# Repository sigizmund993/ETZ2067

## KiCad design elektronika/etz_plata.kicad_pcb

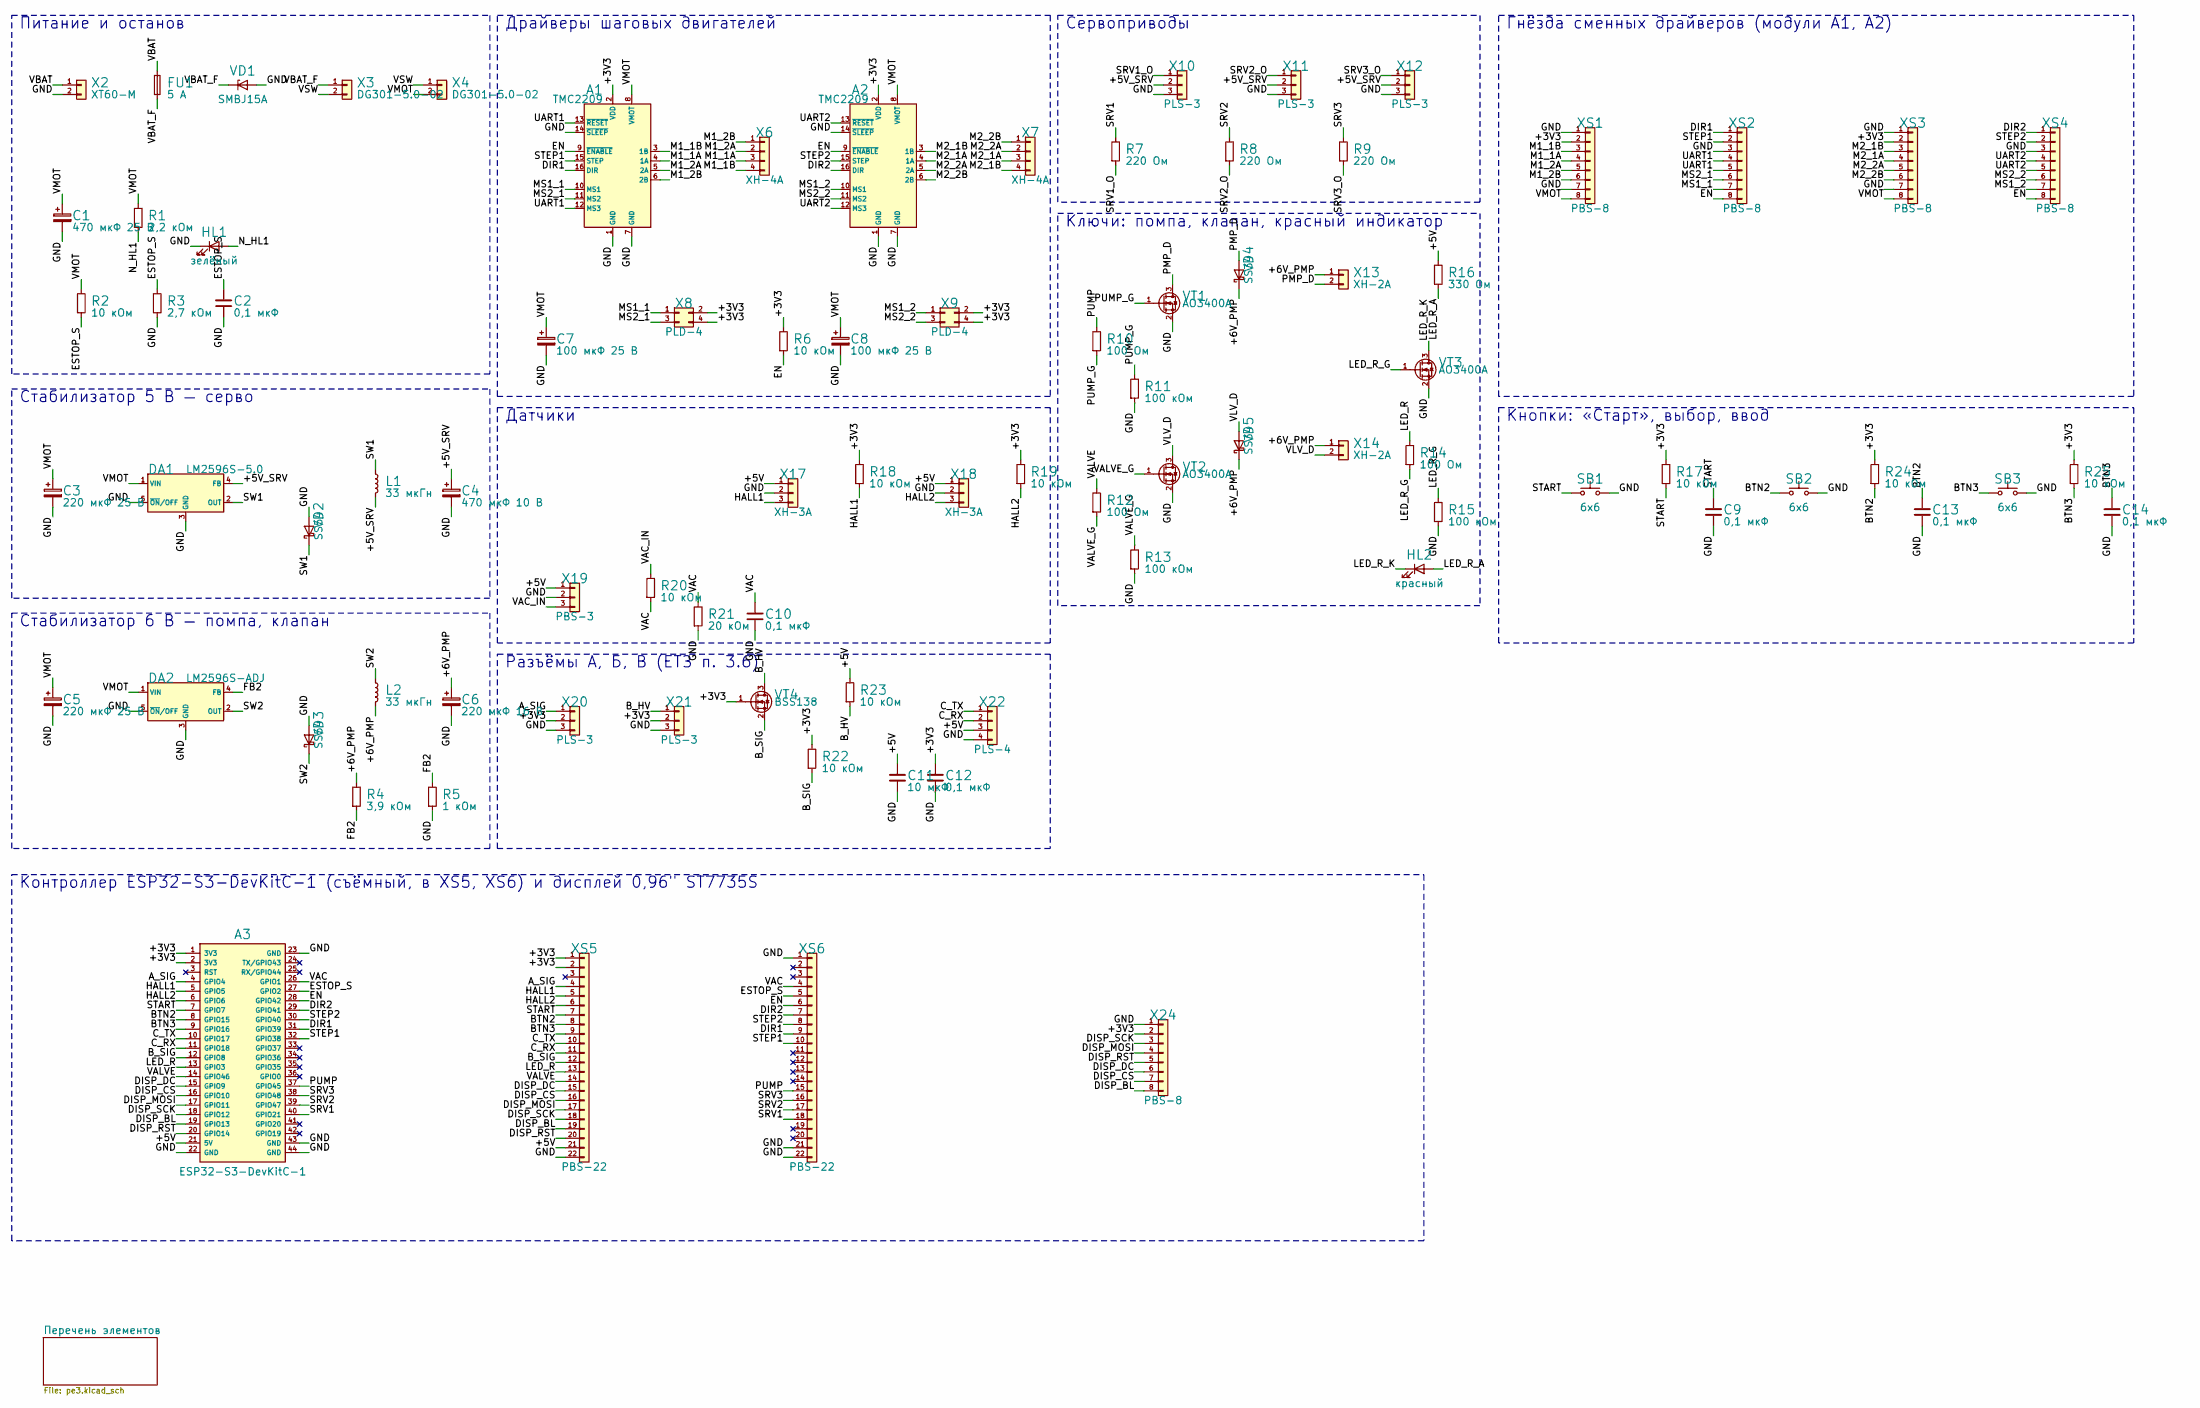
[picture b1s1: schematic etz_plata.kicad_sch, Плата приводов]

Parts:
A1, A2: TMC2209
A3: ESP32-S3-DevKitC-1
C1: 470 мкФ 25 В; CP_Radial_D10.0mm_P5.00mm
C2, C9, C10, C12, C13, C14: 0,1 мкФ; C_0805_2012Metric
C3, C5: 220 мкФ 25 В; CP_Radial_D8.0mm_P3.50mm
C4: 470 мкФ 10 В; CP_Radial_D8.0mm_P3.50mm
C6: 220 мкФ 16 В; CP_Radial_D8.0mm_P3.50mm
C7, C8: 100 мкФ 25 В; CP_Radial_D6.3mm_P2.50mm
C11: 10 мкФ; C_1206_3216Metric
DA1: LM2596S-5.0; TO-263-5_TabPin3
DA2: LM2596S-ADJ; TO-263-5_TabPin3
FU1: 5 А; Fuseholder_Blade_Mini_Keystone_3568
HL1: зелёный; LED_D5.0mm
HL2: красный; LED_D5.0mm
L1, L2: 33 мкГн; L_Bourns_SRR1260
R1: 2,2 кОм; R_0805_2012Metric
R2, R6, R17, R18, R19, R20, R22, R23, R24, R25: 10 кОм; R_0805_2012Metric
R3: 2,7 кОм; R_0805_2012Metric
R4: 3,9 кОм; R_0805_2012Metric
R5: 1 кОм; R_0805_2012Metric
R7, R8, R9: 220 Ом; R_0805_2012Metric
R10, R12, R14: 100 Ом; R_0805_2012Metric
R11, R13, R15: 100 кОм; R_0805_2012Metric
R16: 330 Ом; R_0805_2012Metric
R21: 20 кОм; R_0805_2012Metric
SB1, SB2, SB3: 6x6; SW_PUSH_6mm_H8.5mm
VD1: SMBJ15A; D_SMB
VD2, VD3: SS54; D_SMC
VD4, VD5: SS34; D_SMA
VT1, VT2, VT3: AO3400A; SOT-23
VT4: BSS138; SOT-23
X2: XT60-M; AMASS_XT60-M_1x02_P7.20mm_Vertical
X3, X4: DG301-5.0-02; TerminalBlock_Phoenix_MKDS-1,5-2-5.08_1x02_P5.08mm_Horizont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
X6, X7: XH-4A; JST_XH_B4B-XH-A_1x04_P2.50mm_Vertical
X8, X9: PLD-4; PinHeader_2x02_P2.54mm_Vertical
X10, X11, X12, X20, X21: PLS-3; PinHeader_1x03_P2.54mm_Vertical
X13, X14: XH-2A; JST_XH_B2B-XH-A_1x02_P2.50mm_Vertical
X17, X18: XH-3A; JST_XH_B3B-XH-A_1x03_P2.50mm_Vertical
X19: PBS-3; PinSocket_1x03_P2.54mm_Vertical
X22: PLS-4; PinHeader_1x04_P2.54mm_Vertical
X24: PBS-8; PinSocket_1x08_P2.54mm_Vertical
XS1, XS2, XS3, XS4: PBS-8; PinSocket_1x08_P2.54mm_Vertical
XS5, XS6: PBS-22; PinSocket_1x22_P2.54mm_Vertical

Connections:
/+3V3: A1.2 (VDD), A2.2 (VDD), A3.1 (3V3), A3.2 (3V3), C12.1, R6.1, R17.1, R18.1, R19.1, R22.1, R24.1, R25.1, VT4.1 (G), X8.2, X8.4, X9.2, X9.4, X20.2, X21.2, X24.2, XS1.2, XS3.2, XS5.1, XS5.2
/+5V: A3.21 (5V), C11.1, R16.1, R23.1, X17.1, X18.1, X19.1, X22.3, XS5.21
/+5V_SRV: C4.1, DA1.4 (FB), L1.2, X10.2, X11.2, X12.2
/+6V_PMP: C6.1, L2.2, R4.1, VD4.1 (K), VD5.1 (K), X13.1, X14.1
/A_SIG: A3.4 (GPIO4), X20.1, XS5.4
/BTN2: A3.8 (GPIO15), C13.1, R24.2, SB2.1, XS5.8
/BTN3: A3.9 (GPIO16), C14.1, R25.2, SB3.1, XS5.9
/B_HV: R23.2, VT4.3 (D), X21.1
/B_SIG: A3.12 (GPIO8), R22.2, VT4.2 (S), XS5.12
/C_RX: A3.11 (GPIO18), X22.2, XS5.11
/C_TX: A3.10 (GPIO17), X22.1, XS5.10
/DIR1: A1.16 (DIR), A3.31 (GPIO39), XS2.1, XS6.9
/DIR2: A2.16 (DIR), A3.29 (GPIO41), XS4.1, XS6.7
/DISP_BL: A3.19 (GPIO13), X24.8, XS5.19
/DISP_CS: A3.16 (GPIO10), X24.7, XS5.16
/DISP_DC: A3.15 (GPIO9), X24.6, XS5.15
/DISP_MOSI: A3.17 (GPIO11), X24.4, XS5.17
/DISP_RST: A3.20 (GPIO14), X24.5, XS5.20
/DISP_SCK: A3.18 (GPIO12), X24.3, XS5.18
/EN: A1.9 (~ENABLE), A2.9 (~ENABLE), A3.28 (GPIO42), R6.2, XS2.8, XS4.8, XS6.6
/ESTOP_S: A3.27 (GPIO2), C2.1, R2.2, R3.1, XS6.5
/FB2: DA2.4 (FB), R4.2, R5.1
/GND: A1.1 (GND), A1.7 (GND), A1.14 (~SLEEP), A2.1 (GND), A2.7 (GND), A2.14 (~SLEEP), A3.22 (GND), A3.23 (GND), A3.43 (GND), A3.44 (GND), C1.2, C2.2, C3.2, C4.2, C5.2, C6.2, C7.2, C8.2, C9.2, C10.2, C11.2, C12.2, C13.2, C14.2, DA1.3 (GND), DA1.5 (~ON/OFF), DA2.3 (GND), DA2.5 (~ON/OFF), HL1.1 (K), R3.2, R5.2, R11.2, R13.2, R15.2, R21.2, SB1.2, SB2.2, SB3.2, VD1.2 (A), VD2.2 (A), VD3.2 (A), VT1.2 (S), VT2.2 (S), VT3.2 (S), X2.2, X10.3, X11.3, X12.3, X17.2, X18.2, X19.2, X20.3, X21.3, X22.4, X24.1, XS1.1, XS1.7, XS2.3, XS3.1, XS3.7, XS4.3, XS5.22, XS6.1, XS6.21, XS6.22
/HALL1: A3.5 (GPIO5), R18.2, X17.3, XS5.5
/HALL2: A3.6 (GPIO6), R19.2, X18.3, XS5.6
/LED_R: A3.13 (GPIO3), R14.1, XS5.13
/LED_R_A: HL2.2 (A), R16.2
/LED_R_G: R14.2, R15.1, VT3.1 (G)
/LED_R_K: HL2.1 (K), VT3.3 (D)
/M1_1A: A1.4 (1A), X6.3, XS1.4
/M1_1B: A1.3 (1B), X6.4, XS1.3
/M1_2A: A1.5 (2A), X6.2, XS1.5
/M1_2B: A1.6 (2B), X6.1, XS1.6
/M2_1A: A2.4 (1A), X7.3, XS3.4
/M2_1B: A2.3 (1B), X7.4, XS3.3
/M2_2A: A2.5 (2A), X7.2, XS3.5
/M2_2B: A2.6 (2B), X7.1, XS3.6
/MS1_1: A1.10 (MS1), X8.1, XS2.7
/MS1_2: A2.10 (MS1), X9.1, XS4.7
/MS2_1: A1.11 (MS2), X8.3, XS2.6
/MS2_2: A2.11 (MS2), X9.3, XS4.6
/N_HL1: HL1.2 (A), R1.2
/PMP_D: VD4.2 (A), VT1.3 (D), X13.2
/PUMP: A3.37 (GPIO45), R10.1, XS6.15
/PUMP_G: R10.2, R11.1, VT1.1 (G)
/SRV1: A3.40 (GPIO21), R7.1, XS6.18
/SRV1_O: R7.2, X10.1
/SRV2: A3.39 (GPIO47), R8.1, XS6.17
/SRV2_O: R8.2, X11.1
/SRV3: A3.38 (GPIO48), R9.1, XS6.16
/SRV3_O: R9.2, X12.1
/START: A3.7 (GPIO7), C9.1, R17.2, SB1.1, XS5.7
/STEP1: A1.15 (STEP), A3.32 (GPIO38), XS2.2, XS6.10
/STEP2: A2.15 (STEP), A3.30 (GPIO40), XS4.2, XS6.8
/SW1: DA1.2 (OUT), L1.1, VD2.1 (K)
/SW2: DA2.2 (OUT), L2.1, VD3.1 (K)
/UART1: A1.12 (MS3), A1.13 (~RESET), XS2.4, XS2.5
/UART2: A2.12 (MS3), A2.13 (~RESET), XS4.4, XS4.5
/VAC: A3.26 (GPIO1), C10.1, R20.2, R21.1, XS6.4
/VAC_IN: R20.1, X19.3
/VALVE: A3.14 (GPIO46), R12.1, XS5.14
/VALVE_G: R12.2, R13.1, VT2.1 (G)
/VBAT: FU1.1, X2.1
/VBAT_F: FU1.2, VD1.1 (K), X3.1
/VLV_D: VD5.2 (A), VT2.3 (D), X14.2
/VMOT: A1.8 (VMOT), A2.8 (VMOT), C1.1, C3.1, C5.1, C7.1, C8.1, DA1.1 (VIN), DA2.1 (VIN), R1.1, R2.1, X4.2, XS1.8, XS3.8
/VSW: X3.2, X4.1

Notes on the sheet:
Питание и останов
Стабилизатор 5 В — серво
Стабилизатор 6 В — помпа, клапан
Драйверы шаговых двигателей
Сервоприводы
Датчики
Разъёмы А, Б, В (ЕТЗ п. 3.6)
Ключи: помпа, клапан, красный индикатор
Гнёзда сменных драйверов (модули A1, A2)
Кнопки: «Старт», выбор, ввод
Контроллер ESP32-S3-DevKitC-1 (съёмный, в XS5, XS6) и дисплей 0,96" ST7735S

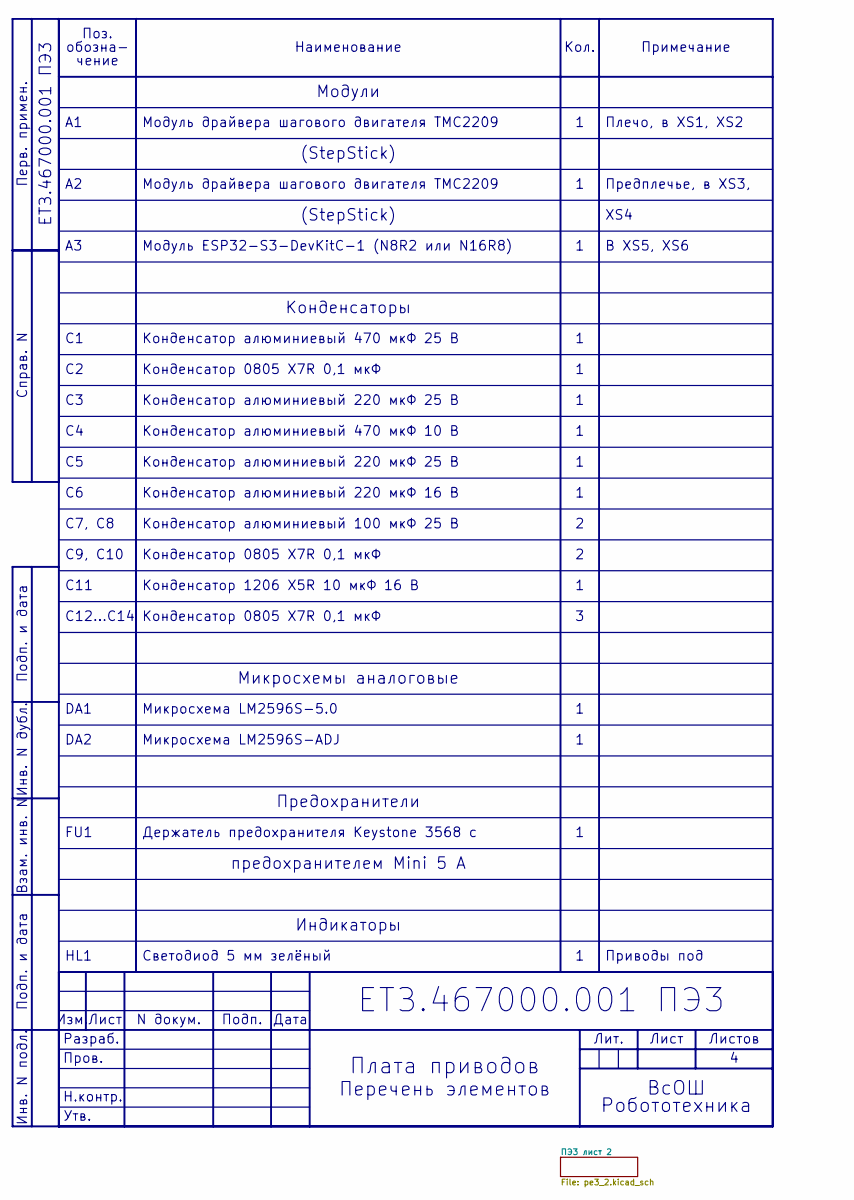
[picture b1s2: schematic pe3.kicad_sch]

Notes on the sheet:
Изм.
Лист
N докум.
Подп.
Дата
Разраб.
Пров.
Н.контр.
Утв.
Лит.
Листов
ЕТЗ.467000.001 ПЭ3
Плата приводов
Перечень элементов
ВсОШ
Робототехника
Инв. N подл.
Подп. и дата
Взам. инв. N
Инв. N дубл.
Перв. примен.
Справ. N
Поз.
обозна-
чение
Наименование
Кол.
Примечание
Модули
Модуль драйвера шагового двигателя TMC2209
Плечо, в XS1, XS2
(StepStick)
Предплечье, в XS3,
XS4
Модуль ESP32-S3-DevKitC-1 (N8R2 или N16R8)
В XS5, XS6
Конденсаторы
Конденсатор алюминиевый 470 мкФ 25 В
Конденсатор 0805 X7R 0,1 мкФ
Конденсатор алюминиевый 220 мкФ 25 В

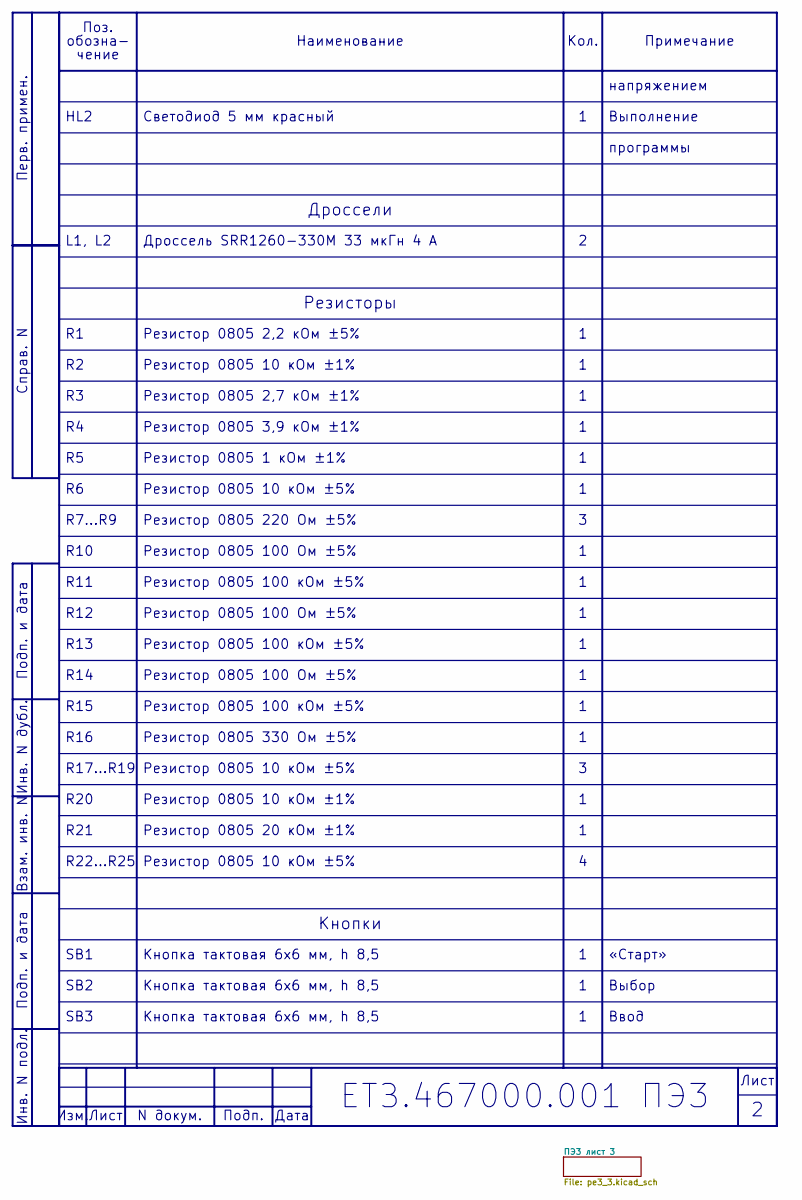
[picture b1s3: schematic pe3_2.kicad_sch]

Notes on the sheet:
Изм.
Лист
N докум.
Подп.
Дата
ЕТЗ.467000.001 ПЭ3
Инв. N подл.
Подп. и дата
Взам. инв. N
Инв. N дубл.
Перв. примен.
Справ. N
Поз.
обозна-
чение
Наименование
Кол.
Примечание
напряжением
HL2
Светодиод 5 мм красный
Выполнение
программы
Дроссели
L1, L2
Дроссель SRR1260-330M 33 мкГн 4 А
Резисторы
Резистор 0805 2,2 кОм ±5%
Резистор 0805 10 кОм ±1%
Резистор 0805 2,7 кОм ±1%
Резистор 0805 3,9 кОм ±1%
Резистор 0805 1 кОм ±1%
Резистор 0805 10 кОм ±5%
R7…R9
Резистор 0805 220 Ом ±5%
R10
Резистор 0805 100 Ом ±5%
R11
Резистор 0805 100 кОм ±5%
R12

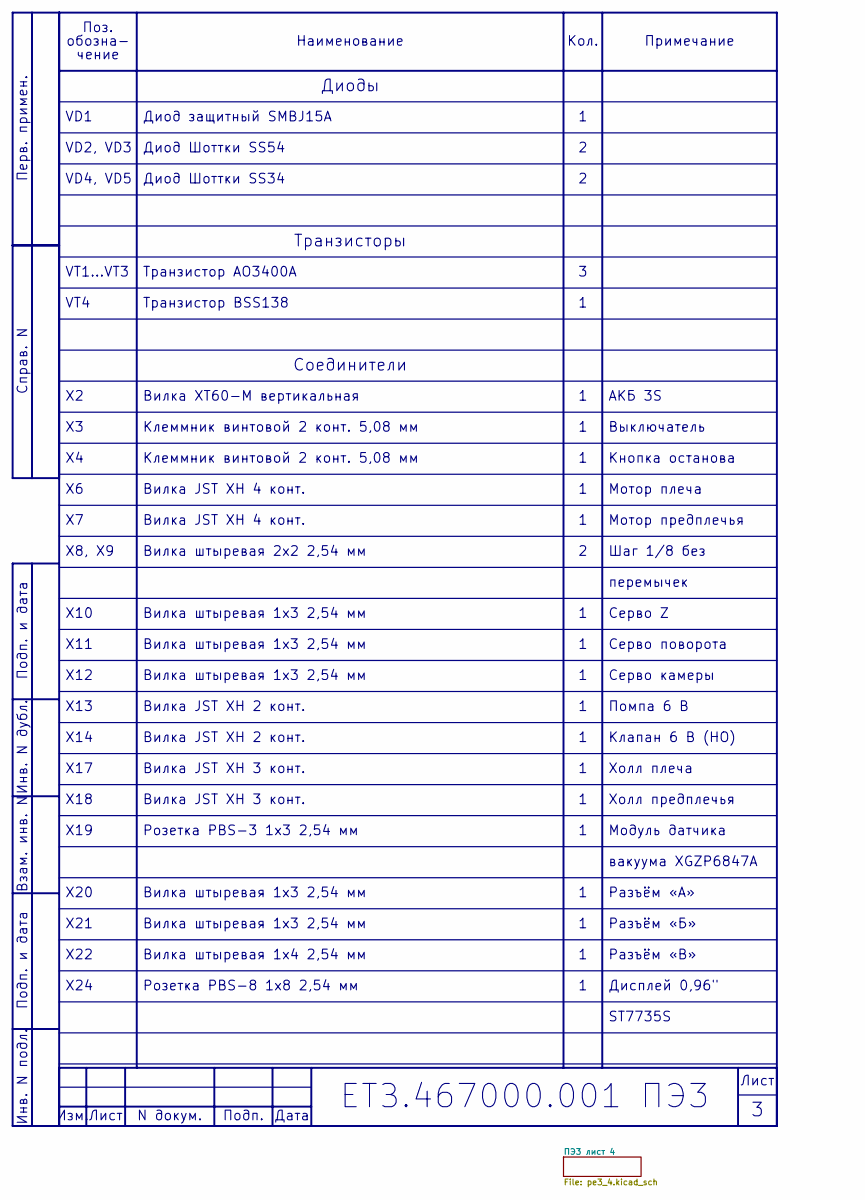
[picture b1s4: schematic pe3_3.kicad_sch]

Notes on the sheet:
Изм.
Лист
N докум.
Подп.
Дата
ЕТЗ.467000.001 ПЭ3
Инв. N подл.
Подп. и дата
Взам. инв. N
Инв. N дубл.
Перв. примен.
Справ. N
Поз.
обозна-
чение
Наименование
Кол.
Примечание
Диоды
VD1
Диод защитный SMBJ15A
VD2, VD3
Диод Шоттки SS54
VD4, VD5
Диод Шоттки SS34
Транзисторы
VT1…VT3
Транзистор AO3400A
VT4
Транзистор BSS138
Соединители
Вилка XT60-M вертикальная
АКБ 3S
Клеммник винтовой 2 конт. 5,08 мм
Выключатель
Кнопка останова
Вилка JST XH 4 конт.
Мотор плеча
Мотор предплечья
X8, X9

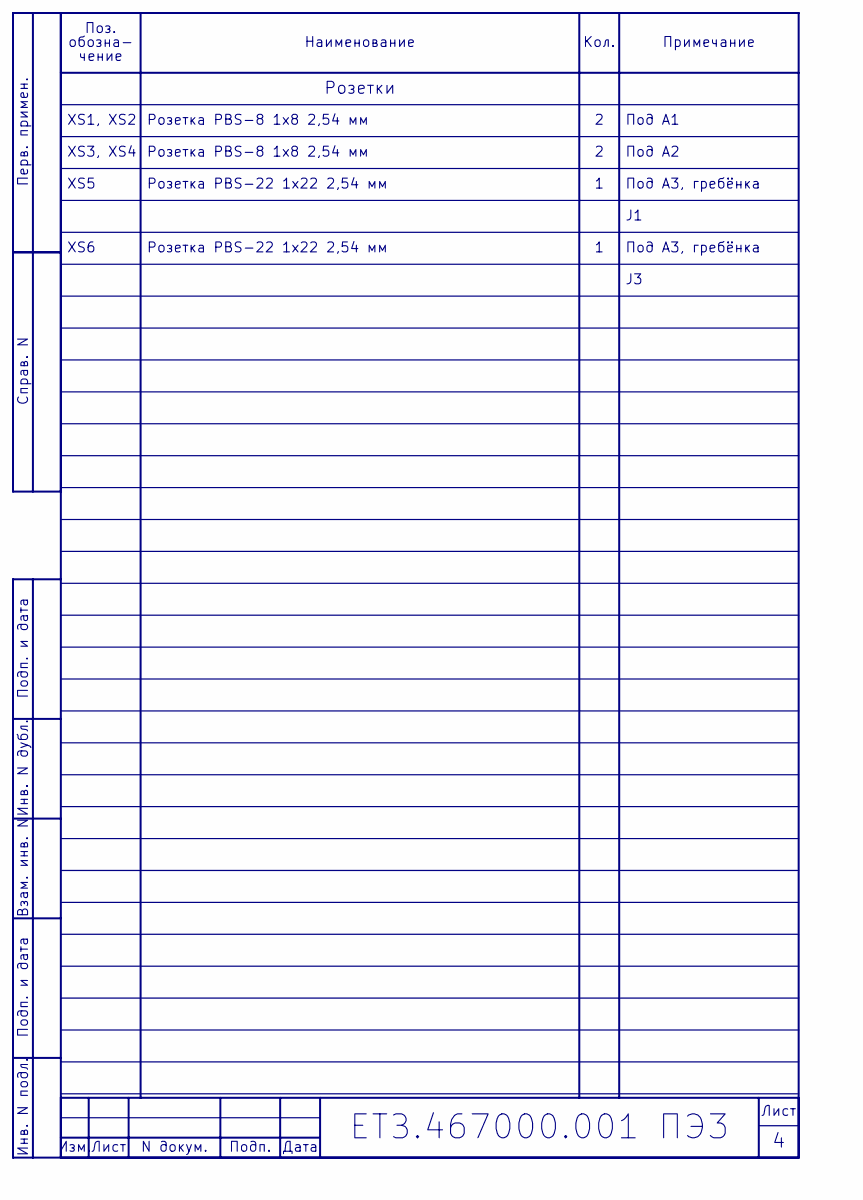
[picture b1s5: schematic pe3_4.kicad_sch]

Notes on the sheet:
Изм.
Лист
N докум.
Подп.
Дата
ЕТЗ.467000.001 ПЭ3
Инв. N подл.
Подп. и дата
Взам. инв. N
Инв. N дубл.
Перв. примен.
Справ. N
Поз.
обозна-
чение
Наименование
Кол.
Примечание
Розетки
XS1, XS2
Розетка PBS-8 1x8 2,54 мм
Под A1
XS3, XS4
Под A2
XS5
Розетка PBS-22 1x22 2,54 мм
Под A3, гребёнка
XS6

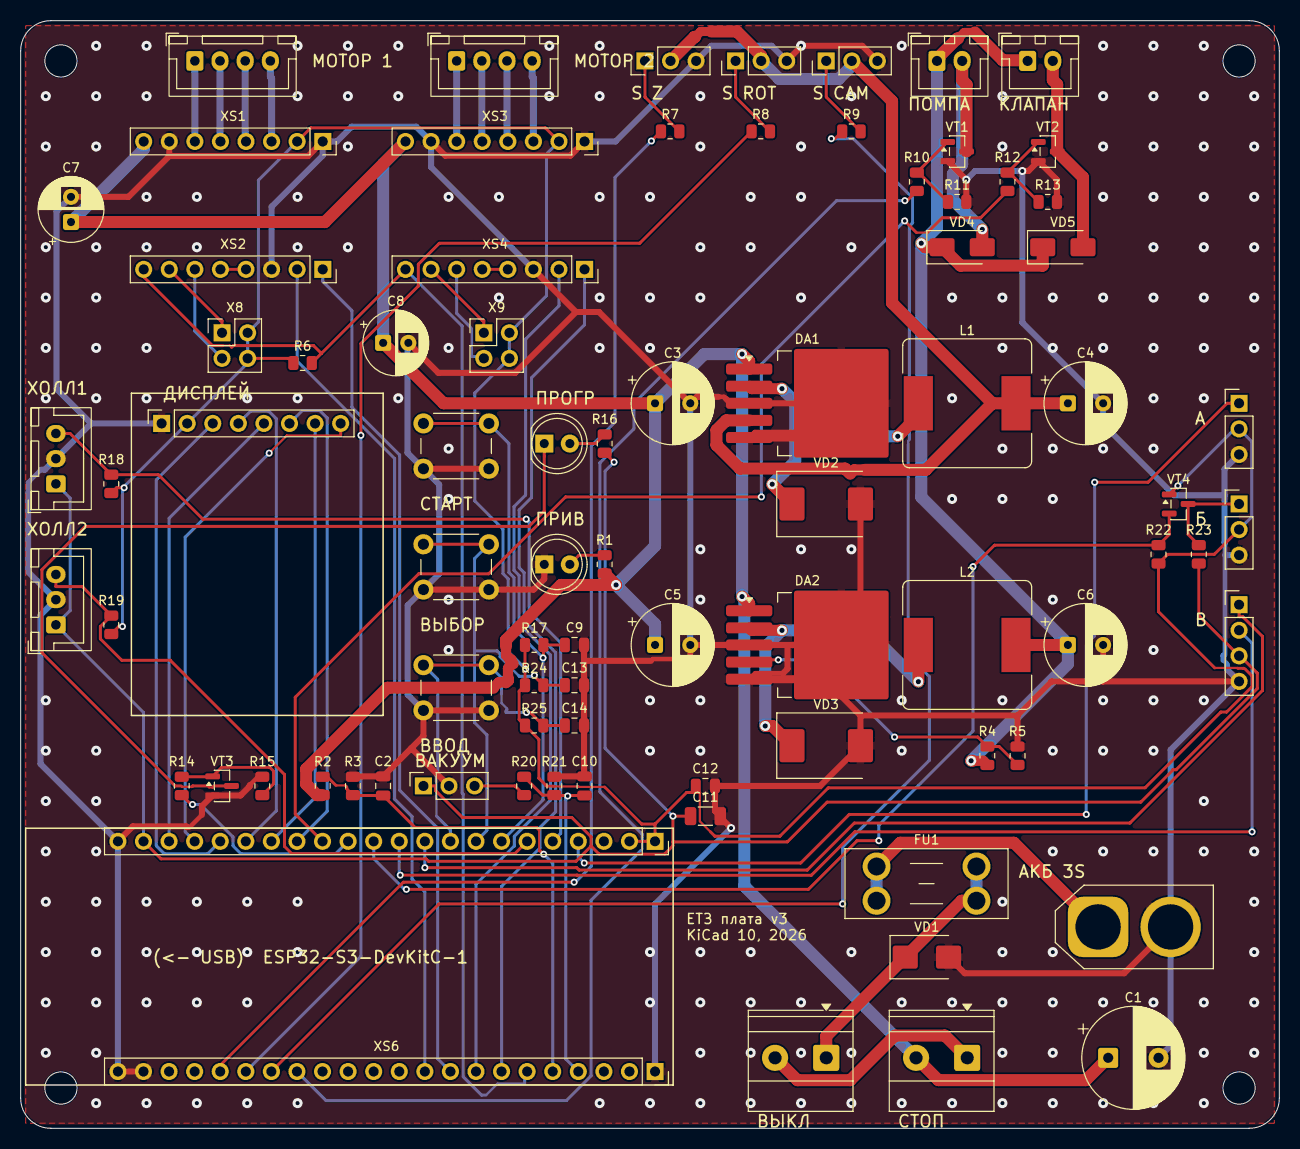
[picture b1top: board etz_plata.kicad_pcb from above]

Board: 2 copper layers, 125.0 x 110.0 mm, 87 parts (0 on the bottom side), 67 nets.

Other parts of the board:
H1, H2, H3, H4: M3; MountingHole_3.2mm_M3

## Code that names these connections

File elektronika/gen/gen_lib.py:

"""Свой символ: ESP32-S3-DevKitC-1 (Espressif, v1.1) -> ../lib/etz.kicad_sym.

Номера выводов: 1..22 — гребёнка J1, 23..44 — J3 (J3-1 = 23). Модуль на плату
не паяется — стоит в гнёздах XS5 (J1) и XS6 (J3), поэтому посадочного места
у символа нет.
"""
import os
import sexp
from sexp import Sym as S

OUT = os.path.join(os.path.dirname(os.path.dirname(os.path.abspath(__file__))), "lib", "etz.kicad_sym")

J1 = ["3V3", "3V3", "RST", "GPIO4", "GPIO5", "GPIO6", "GPIO7", "GPIO15", "GPIO16", "GPIO17", "GPIO18",
      "GPIO8", "GPIO3", "GPIO46", "GPIO9", "GPIO10", "GPIO11", "GPIO12", "GPIO13", "GPIO14", "5V", "GND"]
J3 = ["GND", "TX/GPIO43", "RX/GPIO44", "GPIO1", "GPIO2", "GPIO42", "GPIO41", "GPIO40", "GPIO39", "GPIO38",
      "GPIO37", "GPIO36", "GPIO35", "GPIO0", "GPIO45", "GPIO48", "GPIO47", "GPIO21", "GPIO20", "GPIO19",
      "GND", "GND"]


def eff(size=1.27, hide=False):
    e = [S("effects"), [S("font"), [S("size"), size, size]]]
    if hide:
        e.append([S("hide"), S("yes")])
    return e


def pin(num, name, x, y, ang):
    t = "power_in" if name in ("3V3", "5V", "GND") else ("input" if name == "RST" else "bidirectional")
    return [S("pin"), S(t), S("line"), [S("at"), x, y, ang], [S("length"), 3.81],
            [S("name"), name, eff()], [S("number"), str(num), eff()]]


def main():
    W, n = 15.24, 22
    top = (n - 1) * 2.54 / 2
    body = [S("symbol"), "ESP32-S3-DevKitC-1_0_1",
            [S("rectangle"), [S("start"), -W + 3.81, top + 2.54], [S("end"), W - 3.81, -top - 2.54],
             [S("stroke"), [S("width"), 0.254], [S("type"), S("default")]], [S("fill"), [S("type"), S("background")]]]]
    pins = [S("symbol"), "ESP32-S3-DevKitC-1_1_1"]
    for i, nm in enumerate(J1):
        pins.append(pin(i + 1, nm, -W, top - 2.54 * i, 0))
    for i, nm in enumerate(J3):
        pins.append(pin(23 + i, nm, W, top - 2.54 * i, 180))
    sym = [S("symbol"), "ESP32-S3-DevKitC-1", [S("pin_names"), [S("offset"), 1.016]],
           [S("exclude_from_sim"), S("no")], [S("in_bom"), S("yes")], [S("on_board"), S("yes")],
           [S("property"), "Reference", "A", [S("at"), 0, top + 5.08, 0], eff(1.27)],
           [S("property"), "Value", "ESP32-S3-DevKitC-1", [S("at"), 0, -top - 5.08, 0], eff(1.27)],
           [S("property"), "Footprint", "", [S("at"), 0, 0, 0], eff(1.27, True)],
           [S("property"), "Datasheet",
            "https://docs.espressif.com/projects/esp-dev-kits/en/latest/esp32s3/esp32-s3-devkitc-1/user_guide_v1.1.html",
            [S("at"), 0, 0, 0], eff(1.27, True)],
           [S("property"), "Description", "Плата ESP32-S3-DevKitC-1 (J1: 1-22, J3: 23-44)", [S("at"), 0, 0, 0],
            eff(1.27, True)],
           body, pins]
    lib = [S("kicad_symbol_lib"), [S("version"), 20241209], [S("generator"), "etz_gen"],
           [S("generator_version"), "1.0"], sym]
    os.makedirs(os.path.dirname(OUT), exist_ok=True)
    open(OUT, "w", encoding="utf-8").write(sexp.dump(lib) + "\n")


if __name__ == "__main__":
    main()
